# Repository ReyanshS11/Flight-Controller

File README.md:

# Express Flight Controller
Express is a feature-packed flight controller for drones.

## Key Features
- STM32H743VIT6 microcontroller for speed and performance
- ICM-45686 IMU for precise motion tracking
- BMP581 barometer for accurate altitude data
- NEO-M8U-06B GPS for pinpoint positioning
- Ra-02 RF transmitter for communication
- MicroSD slot for data storage
- USB-C port for program and data transfer
- 2s LiPo battery support and charging with BQ25887RGER
- Connectors for ESC and camera

## Design Features
- The complete flight controller fits within a 70x70mm space.
- Comprised of four layers, front and back copper along with two copper planes for PWR and GND
- Silkscreen for organization and ease of use

## Firmware
The current firmware reads data from all sensors, callibration and further upgrades to be done when PCB is manufactured.
The current firmware is also untested, this will also be done after manufacturing.

## Compatibility
Here are the components I built it for:
- [HGLRC 60A V1 ESC](https://www.getfpv.com/hglrc-60a-v1-2-6s-blheli-s-4-in-1-esc-30-5x30-5.html)
- [Camera](https://www.getfpv.com/fpv/cameras/betafpv-p1-air-unit-hd-vtx.html)
- [Battery](https://motionrc.com/products/admiral-1300mah-2s-7-4v-30c-lipo-battery-with-xt60-connector-epr13002x6)

Although I built it for these components, it should work for pretty much anything that can connect to the JST pins in the same order as the components listed above.

## Why I Built It
I built this both as a wy to learn more about electronics, but also to be able to use this in future projects if I ever make a drone.

## Schematic and Design

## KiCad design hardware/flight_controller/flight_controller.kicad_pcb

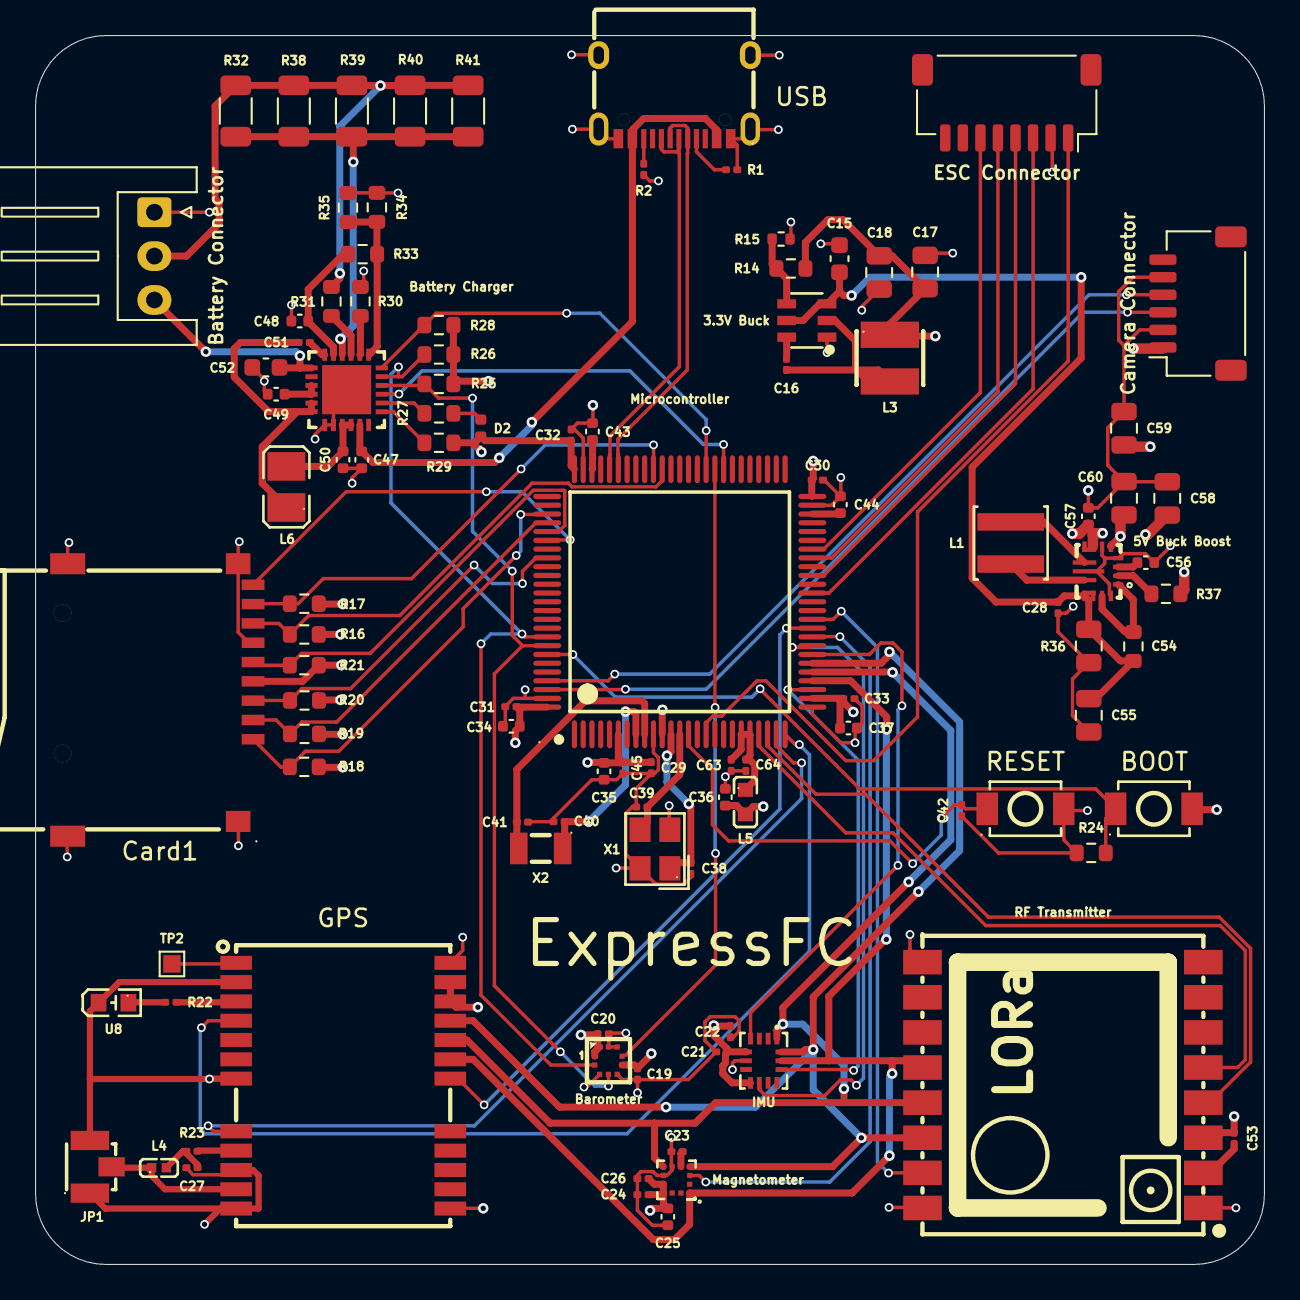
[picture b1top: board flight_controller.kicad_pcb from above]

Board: 4 copper layers, 70.0 x 70.0 mm, 104 parts (0 on the bottom side), 79 nets.

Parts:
3.3V Buck: LMR51430XDDCR; SOT-23-6_L2.9-W1.6-P0.95-LS2.8-BL
5V Buck Boost: TPS63070RNMR; VQFN-15_L3.0-W2.5-P0.50-BL
BOOT: TS-1088-AR02016; SW-SMD_L3.9-W3.0-P4.45
Barometer: BMP581; LGA-10_L2.0-W2.0-P0.50-TL_BMP581
Battery Charger: BQ25887RGER; VFQFPN-24_L4.0-W4.0-P0.50-BL-EP2.8
Battery Connector: Battery_Connector; JST_XH_S3B-XH-A_1x03_P2.50mm_Horizontal
C15: 2.2uF; C_0603_1608Metric
C16, C19, C20, C21, C22, C24, C26, C29, C30, C31, C32, C33, C42, C45, C53, C63, C64: 100nF; C_0201_0603Metric
C17, C18, C58, C59, C60: 22uF; C_0805_2012Metric
C23: 220nF; C_0201_0603Metric
C25, C37, C48, C50, C57: 10uF; C_0402_1005Metric
C27: 47pF; C_0201_0603Metric
C28: 10uF; C_0201_0603Metric
C34, C35, C36, C47: 1uF; C_0402_1005Metric
C38, C39: 20pF; C_0201_0603Metric
C40, C41: 22pF; C_0201_0603Metric
C43, C44: 2.2uF; C_0402_1005Metric
C49: 4.7uF; C_0402_1005Metric
C51: 47nF; C_0201_0603Metric
C52: 10uF; C_0603_1608Metric
C54, C55: 10uF; C_0805_2012Metric
C56: 100nF; C_0402_1005Metric
Camera Connector: Camera_Connector; JST_SH_SM06B-SRSS-TB_1x06-1MP_P1.00mm_Horizontal
Card1: TF-01A; TF-SMD_TF-01A
D2: LED; LED_0402_1005Metric
ESC Connector: ESC_Connector; JST_SH_SM08B-SRSS-TB_1x08-1MP_P1.00mm_Horizontal
GPS: NEO-M8U-06B; GPSM-SMD_24P-L16.0-W12.2-P1.10-TL
IMU: ICM-45686; LGA-14_L3.0-W2.5-P0.50-TL
JP1: U.FL-R-SMT-1; ANT-SMD_UFL-R-SMT-1-10
L1: XFL4020-152MEC; IND-SMD_L4.0-W4.0-A
L3: YHNR3015-5R6M; IND-SMD_L3.0-W3.0
L4: LQG15HN27NJ02D; L0402
L5: FCM1608KF-601T03; L0603
L6: DFE252012F-1R0M=P2; L2520
Magnetometer: LIS2MDLTR; VLGA-12_L2.0-W2.0-P0.50-BL
Microcontroller: STM32H743VIT6_C114409; LQFP-100_L14.0-W14.0-P0.50-LS16.0-BL
R1, R2: 5.1K; R_0201_0603Metric
R14, R37: 100K; R_0603_1608Metric
R15: 22.1K; R_0402_1005Metric
R16, R17, R18, R19, R20, R21, R24, R25, R26, R27, R28, R29, R35, R36: 10K; R_0603_1608Metric
R22: 120; R_0201_0603Metric
R23: 10; R_0201_0603Metric
R30: 383; R_0603_1608Metric
R31: 300; R_0603_1608Metric
R32, R38, R39, R40, R41: 75; R_1206_3216Metric
R33: 5.23K; R_0603_1608Metric
R34: 30.1K; R_0603_1608Metric
RESET: TS-1088-AR02016; SW-SMD_L3.9-W3.0-P4.45
RF Transmitter: RA-02; WIRELM-SMD_RA-02-BL
TP2: TestPoint; TestPoint_Pad_1.0x1.0mm
U8: YLED0603G; LED0603-FD
USB: TYPE-C 16PIN 2MD; USB-C-SMD_TYPE-C-16PIN-2MD-073
X1: X322525MOB4SI; CRYSTAL-SMD_4P-L3.2-W2.5-BL
X2: Q13FC1350000400; FC-135R_L3.2-W1.5

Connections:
+3.3V: BOOT.1, Barometer.1 (VDDIO), Barometer.6 (CSB), Barometer.10 (VDD), C17.1, C18.1, C19.1, C20.1, C21.1, C22.1, C24.1, C25.1, C26.1, C29.1, C30.1, C31.1, C32.1, C33.1, C34.1, C35.1, C36.1, C37.1, C45.1, C53.1, Card1.4 (VDD), D2.1 (K), GPS.22 (V_BCKP), GPS.23 (VCC), IMU.5 (VDDIO), IMU.8 (VDD), L3.2, L5.2, Magnetometer.9 (Vdd), Magnetometer.10 (Vdd_IO), Microcontroller.6 (VBAT), Microcontroller.11 (VDD), Microcontroller.27 (VDD), Microcontroller.50 (VDD), Microcontroller.75 (VDD), Microcontroller.100 (VDD), R14.2, R16.2, R17.2, R18.2, R19.2, R20.2, R21.2, R25.2, R26.2, R28.2, R29.2, RF Transmitter.3 (3.3V)
+5V: 5V Buck Boost.5 (FB), 5V Buck Boost.7 (Vout), C57.1, C58.2, C59.2, C60.2, Camera Connector.1, R37.2
/BMP_INT: Barometer.7 (INT), Microcontroller.59 (PD12)
/BOOT: BOOT.2, Microcontroller.94 (BOOT0), R24.2
/BQ_CE: Battery Charger.3 (CD), Microcontroller.58 (PD11)
/BQ_INT: Battery Charger.6 (~INT), Microcontroller.60 (PD13), R28.1
/BQ_PG: Battery Charger.1 (~PG), R29.1
/CAM_RX: Camera Connector.3, Microcontroller.98 (PE1)
/CAM_TX: Camera Connector.4, Microcontroller.97 (PE0)
/ESC_BAT: ESC Connector.1, Microcontroller.16 (PC1)
/ESC_M1: ESC Connector.3, Microcontroller.39 (PE9)
/ESC_M2: ESC Connector.4, Microcontroller.41 (PE11)
/ESC_M3: ESC Connector.5, Microcontroller.43 (PE13)
/ESC_M4: ESC Connector.6, Microcontroller.44 (PE14)
/GPS_CS: GPS.18 (SDA/SPICS_N), Microcontroller.35 (PB1)
/GPS_EXTINT: GPS.4 (EXTINT), Microcontroller.25 (PA3)
/GPS_RESET: GPS.8 (RESET_N), Microcontroller.24 (PA2)
/HSE_IN: C38.1, Microcontroller.12 (PH0-OSC_IN), X1.1 (OSC1)
/HSE_OUT: C39.1, Microcontroller.13 (PH1-OSC_OUT), X1.3 (OSC2)
/I2C_SCL: Barometer.2 (SCK), Battery Charger.5 (SCL), Microcontroller.92 (PB6), R26.1
/I2C_SDA: Barometer.4 (SDI), Battery Charger.4 (SDA), Microcontroller.93 (PB7), R25.1
/ICM_CS: IMU.12 (AP_CS), Microcontroller.28 (PA4)
/ICM_INT1: IMU.4 (INT1/INT), Microcontroller.32 (PC4)
/ICM_INT2: IMU.9 (INT2/FSYNC/CLKIN), Microcontroller.33 (PC5)
/LSE_IN: C40.1, Microcontroller.8 (PC14-OSC32_IN), X2.1
/LSE_OUT: C41.1, Microcontroller.9 (PC15-OSC32_OUT), X2.2
/MAG_CS: Magnetometer.3 (CS), Microcontroller.34 (PB0)
/RESET: C42.2, Microcontroller.14 (NRST), RESET.2
/RF_CS: Microcontroller.36 (PB2), RF Transmitter.15 (NSS)
/RF_DIO0: Microcontroller.22 (PA0), RF Transmitter.5 (DIO0)
/RF_IN: GPS.11 (RF_IN), JP1.2 (SIN), L4.1
/RF_RESET: Microcontroller.23 (PA1), RF Transmitter.4 (RESET)
/SD_CD: Card1.9 (CD), Microcontroller.81 (PD0)
/SD_CLK: Card1.5 (CLK(SCLK)), Microcontroller.80 (PC12), R21.1
/SD_CMD: Card1.3 (CMD(DI)), Microcontroller.83 (PD2), R20.1
/SD_DAT0: Card1.7 (DAT0(D0)), Microcontroller.65 (PC8), R16.1
/SD_DAT1: Card1.8 (DAT1(RSV)), Microcontroller.66 (PC9), R17.1
/SD_DAT2: Card1.1 (DAT2(RSV)), Microcontroller.78 (PC10), R18.1
/SD_DAT3: Card1.2 (CDDAT3(CS)), Microcontroller.79 (PC11), R19.1
/SPI_SCK: GPS.19 (SCL/SPICLK), IMU.13 (AP_SCL/AP_SCLK), Magnetometer.1 (SCL/SPC), Microcontroller.29 (PA5), RF Transmitter.12 (SCK)
/SPI_SDI: GPS.21 (RXD/SPIMOSI), IMU.14 (AP_SDA/AP_SDIO/AP_SDI), Magnetometer.4 (SDA/SDI/SDO), Microcontroller.31 (PA7), RF Transmitter.14 (MOSI)
/SPI_SDO: GPS.20 (TXD/SPIMISO), IMU.1 (AP_SDO/AP_AD0), Magnetometer.7 (INT/DRDY/SDO), Microcontroller.30 (PA6), RF Transmitter.13 (MISO)
/USB_DN: Microcontroller.70 (PA11), USB.A7 (Dn1), USB.B7 (Dn2)
/USB_DP: Microcontroller.71 (PA12), USB.A6 (Dp1), USB.B6 (Dp2)
GND: 3.3V Buck.1 (GND), 5V Buck Boost.4 (GND), 5V Buck Boost.6 (FB2), 5V Buck Boost.10 (PGND), 5V Buck Boost.15 (Vsel), Barometer.3 (VSS), Barometer.5 (SDO), Barometer.8 (VSS), Barometer.9 (VSS), Battery Charger.19 (GND), Battery Charger.20 (GND), Battery Charger.24 (PSEL), Battery Charger.25 (EP), Battery Connector.1, C15.2, C17.2, C18.2, C19.2, C20.2, C21.2, C22.2, C23.2, C24.2, C25.2, C26.2, C27.2, C28.2, C29.2, C30.2, C31.2, C32.2, C33.2, C34.2, C35.2, C36.2, C37.2, C38.2, C39.2, C40.2, C41.2, C42.1, C43.2, C44.2, C45.2, C47.1, C48.1, C49.2, C50.1, C52.2, C53.2, C54.2, C55.2, C56.1, C57.2, C58.1, C59.1, C60.1, C63.1, C64.1, Camera Connector.2, Camera Connector.5, Card1.6 (VSS), Card1.10 (GND), Card1.11 (GND), Card1.12 (GND), Card1.13 (GND), ESC Connector.2, GPS.2 (D_SEL), GPS.7 (VDD_USB), GPS.10 (GND), GPS.12 (GND), GPS.13 (GND), GPS.24 (GND), IMU.6 (GND), JP1.1 (GND), JP1.3 (GND), Magnetometer.6 (GND), Magnetometer.8 (GND), Microcontroller.10 (VSS), Microcontroller.19 (VSSA), Microcontroller.26 (VSS), Microcontroller.49 (VSS), Microcontroller.74 (VSS), Microcontroller.99 (VSS), R1.2, R2.2, R15.1, R24.1, R30.2, R34.1, R35.1, RESET.1, RF Transmitter.1 (GND), RF Transmitter.2 (GND), RF Transmitter.9 (GND), RF Transmitter.16 (GND), U8.2 (-), USB.13 (EH), USB.14 (EH), USB.A1B12 (GND), USB.B1A12 (GND), X1.2 (GND), X1.4 (GND)
unnamed: C27.1, L4.2, R23.1
unnamed: C43.1, Microcontroller.73 (VCAP)
unnamed: C44.1, Microcontroller.48 (VCAP)
unnamed: Battery Charger.15 (SNS), Battery Charger.16 (SNS), C49.1
unnamed: Battery Charger.21 (PMID), Battery Charger.22 (PMID), C50.2, L6.2
unnamed: Battery Charger.17 (SW), Battery Charger.18 (SW), C51.2, L6.1
unnamed: D2.2 (A), R27.2
unnamed: Battery Connector.2, R31.2, R32.2, R38.2, R39.2, R40.2, R41.2
unnamed: Battery Charger.13 (BAT), Battery Charger.14 (BAT), Battery Connector.3, C52.1
unnamed: 5V Buck Boost.1 (PS/SYNC), 5V Buck Boost.14 (EN), R36.2
unnamed: 5V Buck Boost.11 (L1), L1.1
unnamed: 5V Buck Boost.9 (L2), L1.2
unnamed: 5V Buck Boost.2 (PG), R37.1
unnamed: 5V Buck Boost.3 (Vaux), C56.2
unnamed: 3.3V Buck.6 (CB), C16.1
unnamed: 3.3V Buck.4 (FB), R14.1, R15.2
unnamed: 3.3V Buck.2 (SW), C16.2, L3.1
unnamed: C23.1, Magnetometer.5 (C1)
unnamed: GPS.1 (SAFEBOOT_N), TP2.1 (1_1)
unnamed: GPS.3 (TIMEPULSE), R22.2
unnamed: GPS.9 (VCC_RF), R23.2
unnamed: R22.1, U8.1 (+)
unnamed: C63.2, C64.2, L5.1, Microcontroller.20 (VREF+), Microcontroller.21 (VDDA)
unnamed: Battery Charger.12 (BTST), C51.1
unnamed: Battery Charger.10 (CBSET), R32.1, R38.1, R39.1, R40.1, R41.1
unnamed: Battery Charger.8 (ILIM), R30.1
unnamed: Battery Charger.9 (MID), R31.1
unnamed: Battery Charger.2 (STAT), R27.1
unnamed: Battery Charger.7 (TS), R33.1, R34.2, R35.2
unnamed: R1.1, USB.A5 (CC1)
unnamed: R2.1, USB.B5 (CC2)
VBUS: Battery Charger.23 (VBUS), C47.2, USB.A4B9 (VBUS), USB.B4A9 (VBUS)
VREGN: Battery Charger.11 (REGN), C48.2, R33.2
VSYS: 3.3V Buck.3 (VIN), 3.3V Buck.5 (EN), 5V Buck Boost.12 (Vin), C15.1, C28.1, C54.1, C55.1, R36.1

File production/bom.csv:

Designator,Footprint,Quantity,Value,LCSC Part #
U3,SOT-23-6_L2.9-W1.6-P0.95-LS2.8-BL,1,LMR51430XDDCR,C5185863
U2,VQFN-15_L3.0-W2.5-P0.50-BL,1,TPS63070RNMR,C109322
BAROMETER,LGA-10_L2.0-W2.0-P0.50-TL_BMP581,1,BMP581,C5362283
U12,VFQFPN-24_L4.0-W4.0-P0.50-BL-EP2.8,1,BQ25887RGER,C2761614
J5,JST_XH_S3B-XH-A_1x03_P2.50mm_Horizontal,1,Battery_Connector,
"BOOT, RESET",SW-SMD_L3.9-W3.0-P4.45,2,TS-1088-AR02016,C720477
C15,603,1,2.2uF,
"C16, C19, C20, C21, C22, C24, C26, C29, C30, C31, C32, C33, C42, C45, C53, C63, C64",201,17,100nF,
"C17, C18, C58, C59, C60",805,5,22uF,
C23,201,1,220nF,
"C25, C37, C48, C50, C57",402,5,10uF,
C27,201,1,47pF,
C28,201,1,10uF,
"C34, C35, C36, C47",402,4,1uF,
"C38, C39",201,2,20pF,
"C40, C41",201,2,22pF,
"C43, C44",402,2,2.2uF,
C49,402,1,4.7uF,
C51,201,1,47nF,
C52,603,1,10uF,
"C54, C55",805,2,10uF,
C56,402,1,100nF,
J2,JST_SH_SM06B-SRSS-TB_1x06-1MP_P1.00mm_Horizontal,1,Camera_Connector,
CARD1,TF-SMD_TF-01A,1,TF-01A,C91145
D2,402,1,LED,
J3,JST_SH_SM08B-SRSS-TB_1x08-1MP_P1.00mm_Horizontal,1,ESC_Connector,
GPS,GPSM-SMD_24P-L16.0-W12.2-P1.10-TL,1,NEO-M8U-06B,C7009321
IMU,LGA-14_L3.0-W2.5-P0.50-TL,1,ICM-45686,C22459454
JP1,ANT-SMD_UFL-R-SMT-1-10,1,U.FL-R-SMT-1,C88373
L1,IND-SMD_L4.0-W4.0-A,1,XFL4020-152MEC,C3033018
L3,IND-SMD_L3.0-W3.0,1,YHNR3015-5R6M,C18236327
L4,L0402,1,LQG15HN27NJ02D,C115488
L5,L0603,1,FCM1608KF-601T03,C141723
L6,L2520,1,DFE252012F-1R0M=P2,C435392
MAGNETOMETER,VLGA-12_L2.0-W2.0-P0.50-BL,1,LIS2MDLTR,C919695
MICROCONTROLLER,LQFP-100_L14.0-W14.0-P0.50-LS16.0-BL,1,STM32H743VIT6_C114409,C114409
"R1, R2",201,2,5.1K,
"R14, R37",603,2,100K,
R15,402,1,22.1K,
"R16, R17, R18, R19, R20, R21, R24, R25, R26, R27, R28, R29, R35, R36",603,14,10K,
R22,201,1,120,
R23,201,1,10,
R30,603,1,383,
R31,603,1,300,
"R32, R38, R39, R40, R41",1206,5,75,
R33,603,1,5.23K,
R34,603,1,30.1K,
U1,WIRELM-SMD_RA-02-BL,1,RA-02,C90039
TP2,TestPoint_Pad_1.0x1.0mm,1,TestPoint,
U8,LED0603-FD,1,YLED0603G,C19273151
USB,USB-C-SMD_TYPE-C-16PIN-2MD-073,1,TYPE-C 16PIN 2MD,C2765186
X1,CRYSTAL-SMD_4P-L3.2-W2.5-BL,1,X322525MOB4SI,C9006
X2,FC-135R_L3.2-W1.5,1,Q13FC1350000400,C32346

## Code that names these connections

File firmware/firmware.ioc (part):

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Mcu.Name=STM32H743VITx
Mcu.Package=LQFP100
Mcu.UserName=STM32H743VITx
PA0.GPIOParameters=GPIO_Label
PA0.GPIO_Label=RF_DIO0
PA0.Signal=GPXTI0
PA1.GPIOParameters=PinState,GPIO_Label
PA1.GPIO_Label=RF_RESET
PA1.PinState=GPIO_PIN_SET
PA1.Signal=GPIO_Output
PA11.Mode=Host_Only
PA11.Signal=USB_OTG_FS_DM
PA12.Mode=Host_Only
PA12.Signal=USB_OTG_FS_DP
PA2.GPIOParameters=PinState,GPIO_Label
PA2.GPIO_Label=GPS_RESET
PA2.PinState=GPIO_PIN_SET
PA2.Signal=GPIO_Output
PA3.GPIOParameters=GPIO_Label
PA3.GPIO_Label=GPS_EXTINT
PA3.Signal=GPXTI3
PA4.GPIOParameters=PinState,GPIO_PuPd,GPIO_Label
PA4.GPIO_Label=ICM_CS
PA4.GPIO_PuPd=GPIO_PULLUP
PA4.PinState=GPIO_PIN_SET
PA4.Signal=GPIO_Output
PA5.Mode=Full_Duplex_Master
PA5.Signal=SPI1_SCK
PA6.Mode=Full_Duplex_Master
PA6.Signal=SPI1_MISO
PA7.Mode=Full_Duplex_Master
PA7.Signal=SPI1_MOSI
PB0.GPIOParameters=PinState,GPIO_PuPd,GPIO_Label
PB0.GPIO_Label=MAG_CS
PB0.GPIO_PuPd=GPIO_PULLUP
PB0.PinState=GPIO_PIN_SET
PB0.Signal=GPIO_Output
PB1.GPIOParameters=PinState,GPIO_PuPd,GPIO_Label
PB1.GPIO_Label=GPS_CS
PB1.GPIO_PuPd=GPIO_PULLUP
PB1.PinState=GPIO_PIN_SET
PB1.Signal=GPIO_Output
PB2.GPIOParameters=PinState,GPIO_PuPd,GPIO_Label
PB2.GPIO_Label=RF_CS
PB2.GPIO_PuPd=GPIO_PULLUP
PB2.PinState=GPIO_PIN_SET
PB2.Signal=GPIO_Output
PB6.Mode=I2C
PB6.Signal=I2C1_SCL
PB7.Mode=I2C
PB7.Signal=I2C1_SDA
PC1.GPIOParameters=GPIO_Label
PC1.GPIO_Label=ESC_BAT
PC1.Signal=ADCx_INP11
PC10.Mode=SD_4_bits_Wide_bus
PC10.Signal=SDMMC1_D2
PC11.Mode=SD_4_bits_Wide_bus
PC11.Signal=SDMMC1_D3
PC12.Mode=SD_4_bits_Wide_bus
PC12.Signal=SDMMC1_CK
PC14-OSC32_IN\ (OSC32_IN).Mode=LSE-External-Oscillator
PC14-OSC32_IN\ (OSC32_IN).Signal=RCC_OSC32_IN
PC15-OSC32_OUT\ (OSC32_OUT).Mode=LSE-External-Oscillator
PC15-OSC32_OUT\ (OSC32_OUT).Signal=RCC_OSC32_OUT
PC4.GPIOParameters=GPIO_Label
PC4.GPIO_Label=ICM_INT1
PC4.Signal=GPXTI4
PC5.GPIOParameters=GPIO_Label
PC5.GPIO_Label=ICM_INT2
PC5.Signal=GPXTI5
PC8.Mode=SD_4_bits_Wide_bus
PC8.Signal=SDMMC1_D0
PC9.Mode=SD_4_bits_Wide_bus
PC9.Signal=SDMMC1_D1
PD0.GPIOParameters=GPIO_Label
PD0.GPIO_Label=SD_CS
PD0.Signal=GPIO_Input
PD11.GPIOParameters=GPIO_Label
PD11.GPIO_Label=BQ_CE
PD11.Signal=GPIO_Output
PD12.GPIOParameters=GPIO_Label
PD12.GPIO_Label=BMP_INT
PD12.Signal=GPXTI12
PD13.GPIOParameters=GPIO_Label
PD13.GPIO_Label=BQ_INT
PD13.Signal=GPXTI13
PD2.Mode=SD_4_bits_Wide_bus
PD2.Signal=SDMMC1_CMD
PE0.Mode=Asynchronous
PE0.Signal=UART8_RX
PE1.Mode=Asynchronous
PE1.Signal=UART8_TX
PE11.GPIOParameters=GPIO_Speed,GPIO_Label
PE11.GPIO_Label=ESC_M2
PE11.GPIO_Speed=GPIO_SPEED_FREQ_HIGH
PE11.Signal=S_TIM1_CH2
PE13.GPIOParameters=GPIO_Speed,GPIO_Label
PE13.GPIO_Label=ESC_M3
PE13.GPIO_Speed=GPIO_SPEED_FREQ_HIGH
PE13.Signal=S_TIM1_CH3
PE14.GPIOParameters=GPIO_Speed,GPIO_Label
PE14.GPIO_Label=ESC_M4
PE14.GPIO_Speed=GPIO_SPEED_FREQ_HIGH
PE14.Signal=S_TIM1_CH4
PE9.GPIOParameters=GPIO_Speed,GPIO_Label
PE9.GPIO_Label=ESC_M1
PE9.GPIO_Speed=GPIO_SPEED_FREQ_HIGH
PE9.Signal=S_TIM1_CH1
PH0-OSC_IN\ (PH0).Mode=HSE-External-Oscillator
PH0-OSC_IN\ (PH0).Signal=RCC_OSC_IN
PH1-OSC_OUT\ (PH1).Mode=HSE-External-Oscillator
PH1-OSC_OUT\ (PH1).Signal=RCC_OSC_OUT
RCC.SYSCLKFreq_VALUE=400000000
RCC.SYSCLKSource=RCC_SYSCLKSOURCE_PLLCLK
board=custom
